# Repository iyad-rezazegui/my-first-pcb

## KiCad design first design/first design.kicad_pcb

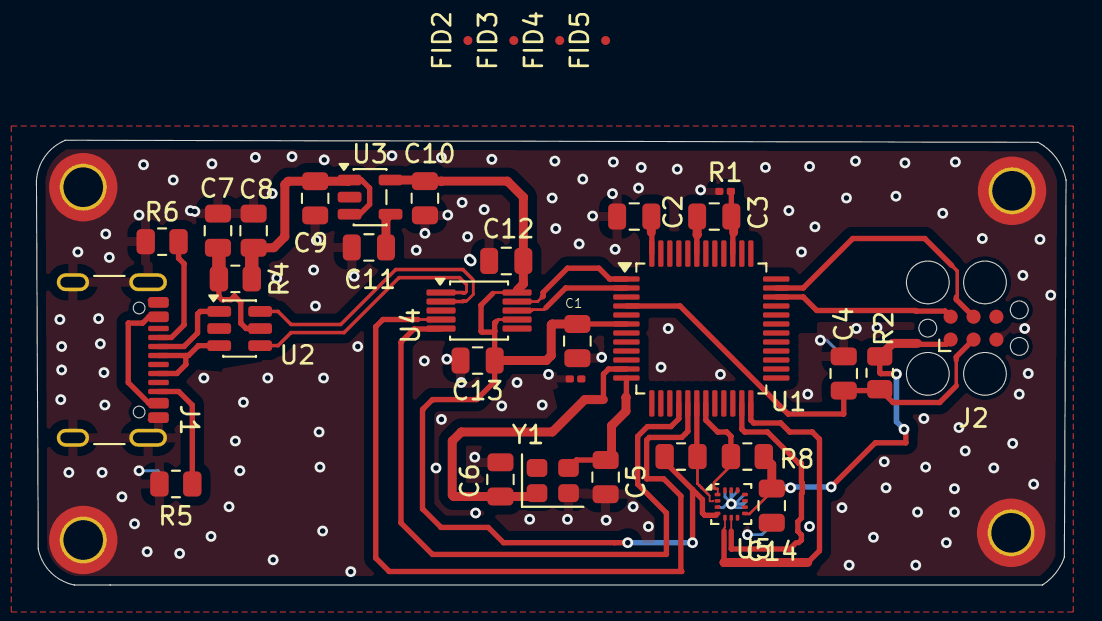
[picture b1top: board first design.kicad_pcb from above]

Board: 2 copper layers, 57.2 x 24.7 mm, 38 parts (0 on the bottom side), 26 nets.

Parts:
C1, C3, C9, C10: 10u; C_0805_2012Metric
C2, C4, C7, C8, C11, C12, C13, C14: 470n; C_0805_2012Metric
C5, C6: 15p; C_0805_2012Metric
FID2, FID3, FID4, FID5: Fiducial; Fiducial_0.5mm_Mask1mm
H1, H2, H3, H4: MountingHole_Pad; MountingHole_2.2mm_M2_DIN965_Pad_TopOnly
J1: USB_C_Receptacle_USB2.0_16P; USB_C_Receptacle_GCT_USB4105-xx-A_16P_TopMnt_Horizontal
J2: Conn_ARM_SWD_TagConnect_TC2030; Tag-Connect_TC2030-IDC-FP_2x03_P1.27mm_Vertical
R1: 0R; R_0201_0603Metric
R2, R5, R6, R7, R8: 5K1; R_0805_2012Metric
R3: 100k; R_0201_0603Metric
R4: 0R; R_0805_2012Metric
U1: LQFP-48_7x7mm_P0.5mm
U2: USBLC6-2SC6; SOT-23-6
U3: SPX3819M5-L-3-3; SOT-23-5
U4: CH340E; MSOP-10_3x3mm_P0.5mm
U5: LIS2DH; LGA-14_2x2mm_P0.35mm_LayoutBorder3x4y
Y1: Crystal_GND24; Crystal_SMD_2520-4Pin_2.5x2.0mm

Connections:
+1V35: C2.1, U1.48 (VSCORE)
+3V3: C1.1, C10.1, C12.1, C13.1, C14.1, J2.1 (VCC), R2.2, R7.2, R8.2, U1.6 (VDD), U3.5 (OUT), U4.7 (VCC), U4.10 (V3), U5.4 (~CS), U5.7 (Vdd_IO), U5.8 (Vdd)
/INT1: U1.23 (PB9), U5.6 (INT1)
/INT2: U1.24 (PB14), U5.5 (INT2)
/NRSET: C4.2, J2.3 (~RESET), R2.1, U1.4 (NRST)
/SCL: R8.1, U1.19 (PA_11), U5.1 (SCL/SPC)
/SDA: R7.1, U1.18 (PA_10), U5.2 (SDA/SDI)
/SWCLK: J2.4 (SWCLK), U1.35 (PA_20)
/SWDIO: J2.2 (SWDIO), U1.34 (PA_19)
/UART0CTS: U1.17 (PA_9), U4.4 (~RTS)
/UART0RTS: U1.16 (PA_8), U4.5 (~CTS)
/UART0RX: U1.2 (PA_1), U4.8 (TXD)
/UART0TX: U1.1 (PA_0), U4.9 (RXD)
/USBCC1: J1.A5 (CC1), R6.2
/USBCC2: J1.B5 (CC2), R5.2
/USBD+: J1.A6 (D+), J1.B6 (D+), U2.3 (I/O2), U2.4 (I/O2), U4.1 (UD+)
/USBD-: J1.A7 (D-), J1.B7 (D-), U2.1 (I/O1), U2.6 (I/O1), U4.2 (UD-)
/VREF+: C3.2, U1.43 (PA_23)
/VREF-: C3.1, R1.2, U1.39 (PA_21)
GND: C1.2, C2.2, C4.1, C5.2, C6.2, C7.2, C8.2, C9.2, C10.2, C11.1, C12.2, C13.2, C14.2, H1.1, H2.1, H3.1, H4.1, J1.A1 (GND), J1.A12 (GND), J1.B1 (GND), J1.B12 (GND), J1.S1 (SHIELD), J2.5 (GND), R1.1, R3.2, R5.1, R6.1, U1.7 (VSS), U2.2 (GND), U3.2 (GND), U4.3 (GND), U5.3 (SDO), U5.9 (GND), U5.10 (GND), U5.11 (GND), U5.12 (GND), U5.13 (GND), U5.14 (GND), Y1.2 (G), Y1.4 (G)
unnamed: R3.1, U1.8 (PA_2_)
unnamed: C6.1, U1.11 (PA_5), Y1.1
unnamed: C5.1, U1.12 (PA_6), Y1.3
unnamed: C11.2, U3.4 (BP)
VBUS: C7.1, J1.A4 (VBUS), J1.A9 (VBUS), J1.B4 (VBUS), J1.B9 (VBUS), R4.1, U2.5 (VBUS)
VBUSF: C8.1, C9.1, R4.2, U3.1 (IN), U3.3 (EN)
